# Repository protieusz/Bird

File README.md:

# Bird
Bird, a variant mod of the Crowboard.  39 keys with a 25mm trackball in the center powered by RP2040-Core A.

# Featured On KBDNews
https://kbd.news/Bird-2471.html

# Full Production Pics

# Descripton
Bird is a heavily modified version of Crowboard which has been blessed by Doesntfazer | Keyboarddweebs.net himself for the mod. [Crowboard](https://github.com/doesntfazer/CrowBoard) was originally designed by Doesntfazer.

# Sponsorship
Thank you  for sponsoring my "BIRD"!
For all your PCB and PCBA needs, PCBWay is your only answer. PCBWay take the time to check the BOM file and the component placement file to make sure that it is up to specs. If there are any issues, PCBWay will email back and inform the customer if there are any corrections that need to be made and also provide solutions for the customer. I highly recommend PCBWay. Great customer service and quality PCBs that you cannot rely on.  I highly recommend them!

# A List Of Mods Made To The Original files by Doesntfazer:

-A circular hole was created in the middle that can accomodate either a 25mm trackball powered by PMW3360 sensor.

-A Chinese "Bird" character was extruded or embross above the trackball in the center. I have also made a "Ironman" theme embross logo case but that case will not be public due to copyright issue. 
Only the "Bird" logo case will be released to the public.

-A Ironman ball holder cover was purchased from AE to cover the 25mm trackball when not in use to prevent the ball from falling off. No I haven't had the time to learn new skills as how to design the
trackball holder to have notches that latches to the ball. The Ironman cover is initially use for push start button for cars. You can also do a search on AE for it. I will not provide the link here.

-Base of the trackball holder with lens cut out is integrated into the top case with integrated 5mm switch plate. Top case sits flush with pcb.

-Additional 3 keys were added below the trackball for use as right click, scroll lock and left click.

-Full keyboard case was created to house the PCB.

-First time I have the hot swappable Kailh PCB being sponsored. As of Aug 30, 2024, the sponsored PCB is still being assembly. As always print the PCB at your own risk.

-Bird is powered by RP2040 Core - A which you can get from AE. I will not provide the link since I don't get anything from the sellers at AE if I endorse it here. Do a search in AE.

-QMK code is borrowed from aki27 bally and modified the matrix to fit my Bird (no pun intended). No suppport will be given since I just copy and paste.

-Use M2 brass hot inserts 3.2mm diameter and 4mm length for the M2 screws to secure the case. I forgot how long is my M2 screws are but they should be greater than 10mm so estimated around 14.6mm. Play around with and buy multiple M2 lenght screws.

# Some Caveats

I printed the Ironman case with parts of the logo imbedded into the USB C case structure and therefore I made the PCB USB C port area extend out a bit but didn't account for the wide of the opening so case doesn't fully close. I will upload the original Bird designed PCB with no mods on the USB C port PCB area. Sponsored PCB was on the Ironman version with changes made to the USB C port PCB. However this version will not be release. Please print the untested "Bird" version. It should work and fit the case. The PCB components and routing designs are the same. Update: Fixed Bird Bottom case uploaded. Please use this instead of the "Bird Case Step". As always please print at your own risk.

# Renders

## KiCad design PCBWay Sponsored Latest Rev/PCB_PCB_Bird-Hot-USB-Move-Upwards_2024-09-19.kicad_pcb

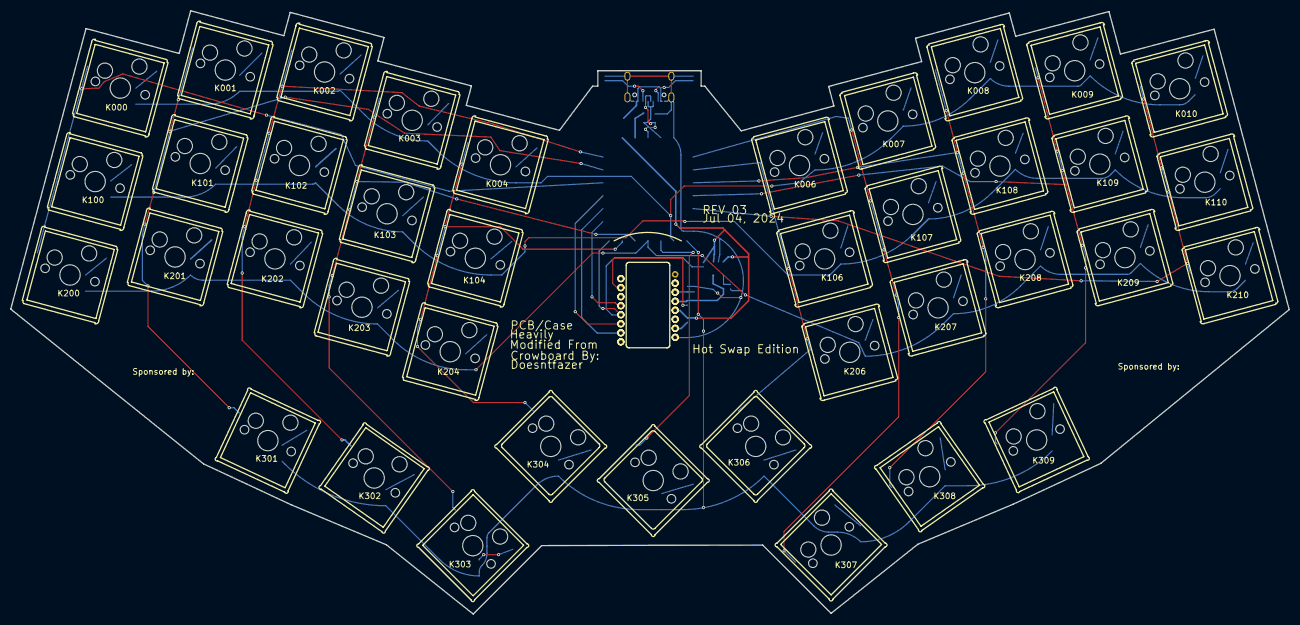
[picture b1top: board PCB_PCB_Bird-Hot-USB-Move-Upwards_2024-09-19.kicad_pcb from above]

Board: 2 copper layers, 251.9 x 118.9 mm, 95 parts (0 on the bottom side), 71 nets.

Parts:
C17, C19, C20: 4.7uF; C0402
C18: 100nF; C0402
D000, D001, D002, D003, D004, D006, D007, D008, D009, D010, D100, D101, D102, D103, D104, D106, D107, D108, D109, D110, D200, D201, D202, D203, D204, D206, D207, D208, D209, D210, D301, D302, D303, D304, D305, D306, D307, D308, D309: DIODE-SOD123
D11: PRTR5V0U2X,215; SOT-143_L2.9-W1.3-P1.92-LS2.3-BR
F1: BSMD0805-020-15V; F0805
K000, K001, K002, K003, K004, K006, K007, K008, K009, K010, K100, K101, K102, K103, K104, K106, K107, K108, K109, K110, K200, K201, K202, K203, K204, K206, K207, K208, K209, K210, K301, K302, K303, K304, K305, K306, K307, K308, K309: Kailh MX Hotswap; KAILH MX HOTSWAP
R1, R2: 5.1kΩ; R0402
R10, R12, R13: 10kΩ; R0402
R11: 39Ω; R0402
R14: 15kΩ; R0402
U1: 5-ROW1; RP2040-CORE-A
U10: AP2127K-ADJTRG1; SOT-23-5_L3.0-W1.7-P0.95-LS2.8-BR
U11: PMW3360DM-T2QU; PMW3360DM-T2QU.PACK
USBC1: TYPE-C-31-M-12; USB-C_SMD-TYPE-C-31-M-12

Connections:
+2V: C20.2, R11.2, R14.2, U10.5, U11.4
+3V3: C19.2, R10.2, R12.2, U1.15, U10.1, U10.3, U11.5
+5V: D11.4, F1.2, U1.16
COL0: K000.2, K100.2, K200.2, U1.11
COL1: K001.2, K101.2, K201.2, K301.2, U1.12
COL2: K002.2, K102.2, K202.2, K302.2, U1.13
COL3: K003.2, K103.2, K203.2, K303.2, U1.5
COL4: K004.2, K104.2, K204.2, K304.2, U1.6
COL5: K305.2, U1.3
COL6: K006.2, K106.2, K206.2, K306.2, U1.21
COL7: K007.2, K107.2, K207.2, K307.2, U1.20
COL8: K008.2, K108.2, K208.2, K308.2, U1.22
COL9: K009.2, K109.2, K209.2, K309.2, U1.23
COL10: K010.2, K110.2, K210.2, U1.24
CS: U1.8, U11.13
D000_A: D000.A, K000.1
D001_A: D001.A, K001.1
D002_A: D002.A, K002.1
D003_A: D003.A, K003.1
D004_A: D004.A, K004.1
D006_A: D006.A, K006.1
D007_A: D007.A, K007.1
D008_A: D008.A, K008.1
D009_A: D009.A, K009.1
D010_A: D010.A, K010.1
D100_A: D100.A, K100.1
D101_A: D101.A, K101.1
D102_A: D102.A, K102.1
D103_A: D103.A, K103.1
D104_A: D104.A, K104.1
D106_A: D106.A, K106.1
D107_A: D107.A, K107.1
D108_A: D108.A, K108.1
D109_A: D109.A, K109.1
D110_A: D110.A, K110.1
D200_A: D200.A, K200.1
D201_A: D201.A, K201.1
D202_A: D202.A, K202.1
D203_A: D203.A, K203.1
D204_A: D204.A, K204.1
D206_A: D206.A, K206.1
D207_A: D207.A, K207.1
D208_A: D208.A, K208.1
D209_A: D209.A, K209.1
D210_A: D210.A, K210.1
D301_A: D301.A, K301.1
D302_A: D302.A, K302.1
D303_A: D303.A, K303.1
D304_A: D304.A, K304.1
D305_A: D305.A, K305.1
D306_A: D306.A, K306.1
D307_A: D307.A, K307.1
D308_A: D308.A, K308.1
D309_A: D309.A, K309.1
D+: D11.3, U1.18, USBC1.A6, USBC1.B6
D-: D11.2, U1.17, USBC1.A7, USBC1.B7
GND: C17.2, C18.2, C19.1, C20.1, D11.1, R1.2, R2.1, R13.1, U1.19, U10.2, U11.8, USBC1.0, USBC1.1, USBC1.2, USBC1.3, USBC1.A1, USBC1.A12, USBC1.B1, USBC1.B12
MISO: R12.1, U1.7, U11.12
MOSI: U1.10, U11.11
R1_1: R1.1, USBC1.A5
R2_2: R2.2, USBC1.B5
ROW0: D000.C, D001.C, D002.C, D003.C, D004.C, D006.C, D007.C, D008.C, D009.C, D010.C, U1.2
ROW1: D100.C, D101.C, D102.C, D103.C, D104.C, D106.C, D107.C, D108.C, D109.C, D110.C, U1.25
ROW2: D200.C, D201.C, D202.C, D203.C, D204.C, D206.C, D207.C, D208.C, D209.C, D210.C, U1.4
ROW3: D301.C, D302.C, D303.C, D304.C, D305.C, D306.C, D307.C, D308.C, D309.C, U1.1
SCK: U1.9, U11.10
U10_4: R13.2, R14.1, U10.4
U11_3: C17.1, C18.1, U11.3
U11_7: R10.1, U11.7
U11_15: R11.1, U11.15
VBUS: F1.1, USBC1.A4, USBC1.A9, USBC1.B4, USBC1.B9

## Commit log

2024-08-29 QMK source
2024-08-29 QMK firmware
2024-08-29 Bird case stls
2024-08-29 PCB DXF
2024-08-29 Production Files Rev3
2024-08-29 Bird Case STEP
2024-09-19 Schematic & converted pcb file
2024-09-19 Use this fixed bottom case.
